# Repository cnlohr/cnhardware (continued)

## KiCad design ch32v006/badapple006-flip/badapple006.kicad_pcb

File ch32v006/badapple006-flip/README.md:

This has been moved to https://github.com/cnlohr/badderapple/tree/master/playback/ch32v006_hardware

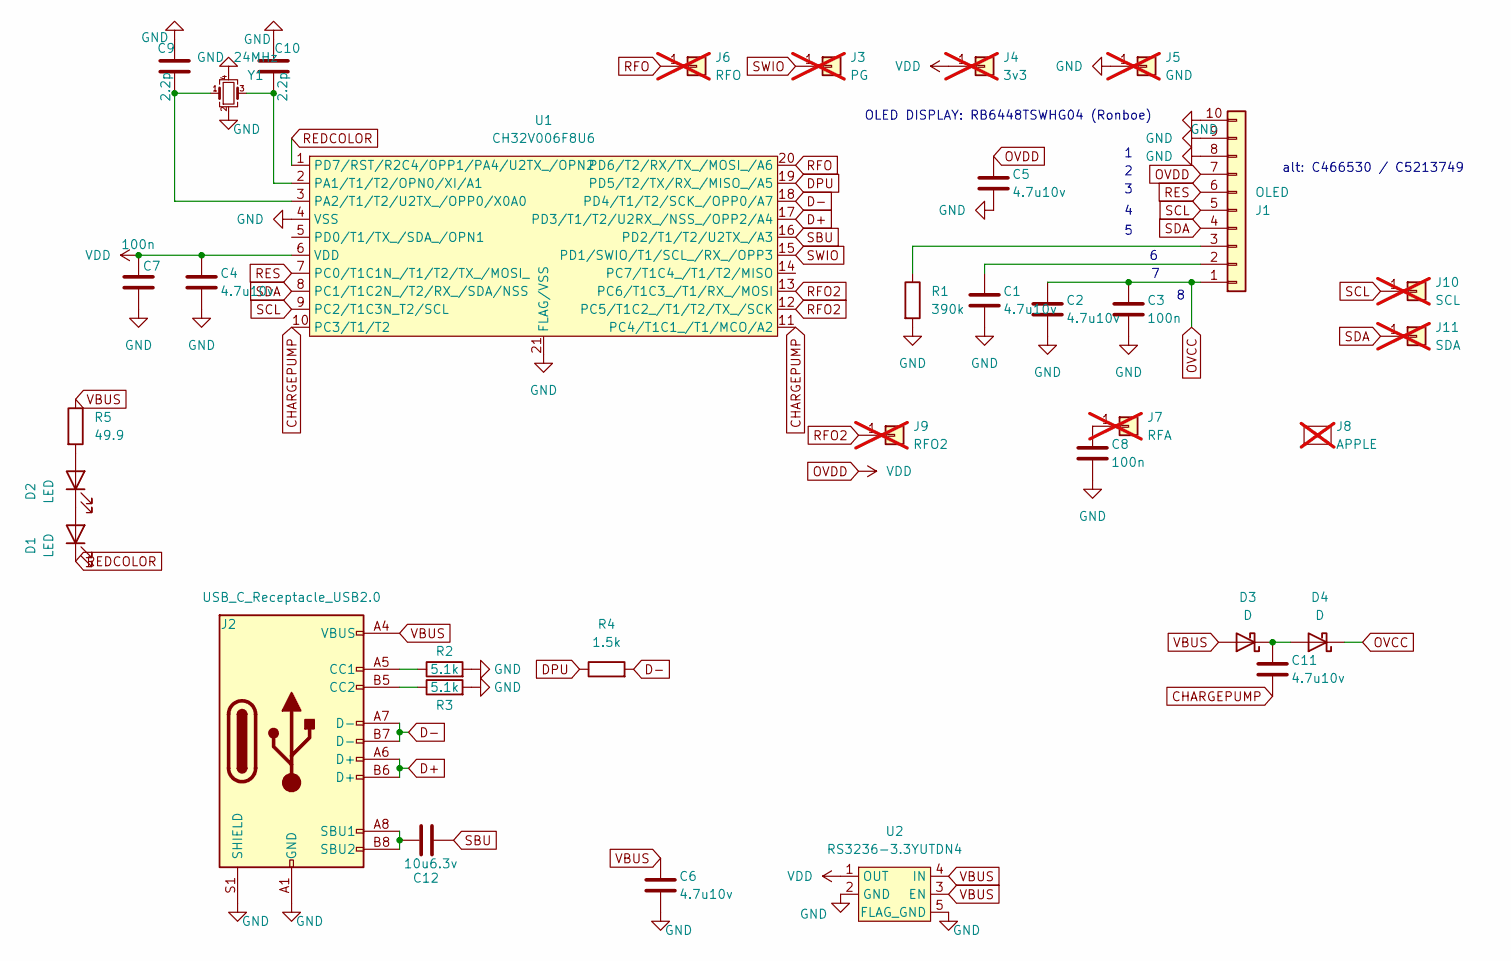
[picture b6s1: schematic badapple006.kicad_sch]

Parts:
C1, C2, C4, C5, C6, C11: 4.7u10v; C_0402_1005Metric; LCSC C23733
C3, C7, C8: 100n; C_0402_1005Metric; LCSC C1525
C9, C10: 2.2p; C_0402_1005Metric; LCSC C1559
C12: 10u6.3v; C_0402_1005Metric; LCSC C15525
D1, D2: LED; LED_0603_1608Metric; LCSC C2286
D3, D4: D; D_SOD-323; LCSC C191023
J1: OLED; AFC42-S08FMA-1H; LCSC C466530
J2: USB_C_Receptacle_USB2.0; USB_C_Receptacle_HRO_TYPE-C-31-M-12; LCSC C2765186
J3: PG; TestPoint_Pad_D1.0mm; not fitted
J4: 3v3; TestPoint_Pad_D1.0mm; not fitted
J5: GND; TestPoint_Pad_D1.0mm; not fitted
J6: RFO; TestPoint_Pad_D1.0mm; not fitted
J7: RFA; TestPoint_Pad_D1.0mm; not fitted
J8: APPLE; apple; not fitted
J9: RFO2; TestPoint_Pad_D1.0mm; not fitted
J10: SCL; TestPoint_Pad_D1.0mm; not fitted
J11: SDA; TestPoint_Pad_D1.0mm; not fitted
R1: 390k; R_0402_1005Metric; LCSC C25782
R2, R3: 5.1k; R_0402_1005Metric; LCSC C105872
R4: 1.5k; R_0402_1005Metric; LCSC C25867
R5: 49.9; R_0402_1005Metric; LCSC C25120
U1: CH32V006F8U6; QFN-20-1EP_3x3mm_P0.4mm_EP1.65x1.65mm; LCSC C42431288
U2: RS3236-3.3YUTDN4; xdfn-reg; LCSC C379350
Y1: 24MHz; Crystal_SMD_2016-4Pin_2.0x1.6mm; LCSC C2929397

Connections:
CHARGEPUMP: C11.2, U1.10 (PC3/T1/T2), U1.11 (PC4/T1C1_/T1/MCO/A2)
D+: J2.A6 (D+), J2.B6 (D+), U1.17 (PD3/T1/T2/U2RX_/NSS_/OPP2/A4)
D-: J2.A7 (D-), J2.B7 (D-), R4.2, U1.18 (PD4/T1/T2/SCK_/OPP0/A7)
DPU: R4.1, U1.19 (PD5/T2/TX/RX_/MISO_/A5)
GND: C1.2, C2.2, C3.2, C4.2, C5.2, C6.2, C7.2, C8.2, C9.1, C10.1, J1.8, J1.9, J1.10, J2.A1 (GND), J2.A12 (GND), J2.B1 (GND), J2.B12 (GND), J2.S1 (SHIELD), J5.1, R1.2, R2.2, R3.2, U1.4 (VSS), U1.21 (FLAG/VSS), U2.2 (GND), U2.5 (FLAG_GND), Y1.2, Y1.4
unnamed: D1.2 (A), D2.1 (K)
unnamed: D2.2 (A), R5.2
unnamed: C11.1, D3.1 (K), D4.2 (A)
unnamed: C1.1, J1.2
unnamed: J1.3, R1.1
unnamed: J2.A5 (CC1), R2.1
unnamed: J2.B5 (CC2), R3.1
unnamed: C12.2, J2.A8 (SBU1), J2.B8 (SBU2)
unnamed: C8.1, J7.1
unnamed: C10.2, U1.2 (PA1/T1/T2/OPN0/XI/A1), Y1.3
unnamed: C9.2, U1.3 (PA2/T1/T2/U2TX_/OPP0/X0A0), Y1.1
OVCC: C2.1, C3.1, D4.1 (K), J1.1
OVDD: C4.1, C5.1, C7.1, J1.7, J4.1, U1.6 (VDD), U2.1 (OUT)
REDCOLOR: D1.1 (K), U1.1 (PD7/RST/R2C4/OPP1/PA4/U2TX_/OPN2)
RES: J1.6, U1.7 (PC0/T1C1N_/T1/T2/TX_/MOSI_)
RFO: J6.1, U1.20 (PD6/T2/RX/TX_/MOSI_/A6)
RFO2: J9.1, U1.12 (PC5/T1C2_/T1/T2/TX_/SCK), U1.13 (PC6/T1C3_/T1/RX_/MOSI)
SBU: C12.1, U1.16 (PD2/T1/T2/U2TX_/A3)
SCL: J1.5, J10.1, U1.9 (PC2/T1C3N_T2/SCL)
SDA: J1.4, J11.1, U1.8 (PC1/T1C2N_/T2/RX_/SDA/NSS)
SWIO: J3.1, U1.15 (PD1/SWIO/T1/SCL_/RX_/OPP3)
VBUS: C6.1, D3.2 (A), J2.A4 (VBUS), J2.A9 (VBUS), J2.B4 (VBUS), J2.B9 (VBUS), R5.1, U2.3 (EN), U2.4 (IN)

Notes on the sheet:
alt: C466530 / C5213749
OLED DISPLAY: RB6448TSWHG04 (Ronboe)

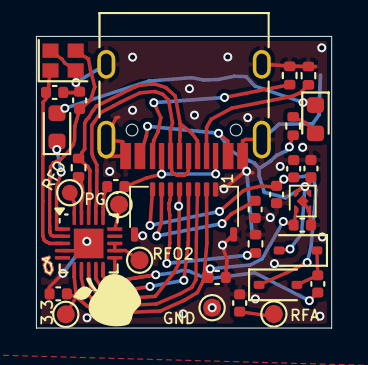
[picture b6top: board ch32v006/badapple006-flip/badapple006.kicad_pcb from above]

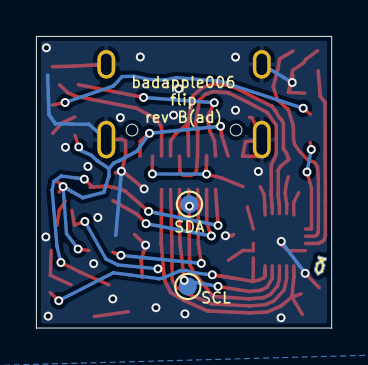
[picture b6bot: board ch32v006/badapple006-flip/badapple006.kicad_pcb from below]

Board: 2 copper layers, 16.4 x 16.2 mm, 35 parts (2 on the bottom side), 27 nets.

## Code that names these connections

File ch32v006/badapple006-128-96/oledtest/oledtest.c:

/* Small example showing how to use the SWIO programming pin to 
   do printf through the debug interface */

#include "ch32fun.h"
#include <stdio.h>

//#define SH1107
// Actually an SSD1327
#define SSD1327
#define SSD1306_FULLUSE
#define SSD1306_W (128) 
#define SSD1306_H (96*4)// For greyscale.
#define SSD1306_FULLUSE
#define SSD1306_OFFSET 0

#define SSD1306_RST_PIN PC3
#define SSD1306_CS_PIN PC1
#define SSD1306_DC_PIN PC2

#define SSD1306_MOSI_PIN PC6
#define SSD1306_SCK_PIN  PC5

#include "ssd1306_spi.h"
#include "ssd1306.h"

int main()
{
	SystemInit();
	funGpioInitAll();

	// On the 006, only GPIO_CFGLR_OUT_10Mhz_PP is available.

	funPinMode( PC4, GPIO_CFGLR_OUT_10Mhz_PP ); // BCTRL to 0.
	funDigitalWrite( PC4, 0 );

	// Power on
	funPinMode( PC0, GPIO_CFGLR_OUT_10Mhz_PP ); // Turn on OLED display.
	funDigitalWrite( PC0, 1 );

	ssd1306_rst();

	if( ssd1306_spi_init() || ssd1306_init() )
	{
		printf( "OLED FAILURE\n" );
	}

	static const uint8_t ssd1327_init_array[] =
	{

		0xAE, // Display off
		0xD5, 0x62, // Function Selection
		0xA8, 0x5F, // Set Multiplex Ratio
		0xA2, 0x20, // Set Display Offset
		0xA1, 0x60, // Set Display Start Line
		0xAB, 0x01, // Enable internal VDD regulator
		0xa0, 0x51, // Set Re-Map
		0xb1, 0x22, // Set phase length
		0x81, 0xdf, // Set Contrast Control
		0xbc, 0x10, // Set Pre-Charge voltage
		0xbe, 0x05, // Set VCOMH Deselect Level

		0xa4, // Normal display

		0xb6, 0x0a, // Set Second pre-charge Period
		0xaf, // Display On

//		0xa0, 0x51, // Set Re-Map

/*
		0xD5, 0x62, // Function Selection
		0xa0, 0x40, // Enable even-odd

		0xA2, 0x40, // Set Display Offset
		0xA1, 0x00, // Set Display Start Line
		0xAB, 0x01, // Enable internal VDD regulator

		0xb1, 0x22, // Set phase length
		0x81, 0xdf, // Set Contrast Control
		0xbc, 0x10, // Set Pre-Charge voltage
		0xbe, 0x05, // Set VCOMH Deselect Level

		// Bonus
		0xA8, 0x5F, // Set Multiplex Ratio
*/
	};
	int i;
	for( i = 0; i < sizeof( ssd1327_init_array ); i++ )
	{
		ssd1306_cmd( ssd1327_init_array[i] );
	}

	int x, y;
	int t = 0;

//	ssd1306_cmd( 0xA2 );
//	ssd1306_cmd( 0x60 );
//	ssd1306_cmd( 0xA1 );
//	ssd1306_cmd( 0x80 );


	while(1)
	{
		for( y = 0; y < 96; y++ )
		{
			for( x = 0; x < 128; x++ )
			{
				int gs = ((x*y+t)>>1)&0xf;
				if( x & 1 )
					ssd1306_buffer[(x>>1)+y*64] |= gs;
				else
					ssd1306_buffer[(x>>1)+y*64] = gs<<4;

				//ssd1306_buffer[(x>>1)+y*64] = y;//(y&1)?0xfa:0x00;
			}
		}
		t++;
		ssd1306_refresh();

/*	ssd1306_cmd( 0xA8 );
	ssd1306_cmd( 0x02 );
	ssd1306_cmd( 0xA8 );
	ssd1306_cmd( 0x3f );
	Delay_Us(100);
	ssd1306_cmd( 0xA8 );
	ssd1306_cmd( 0x02 );
*/
/*
	ssd1306_cmd( 0xA8 );
	ssd1306_cmd( 0x01 ); // Set Multiplex Ratio
	ssd1306_cmd( 0xA8 );
	ssd1306_cmd( 0x0f ); // Set Multiplex Ratio
	ssd1306_cmd( 0xA0 );
	ssd1306_cmd( 0x0f ); // Set start line
*/
	}
}

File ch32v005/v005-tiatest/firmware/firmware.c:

/* Small example showing how to use the SWIO programming pin to 
   do printf through the debug interface */

#include "ch32fun.h"
#include <stdio.h>

int main()
{
	SystemInit();

	RCC->APB2PCENR = RCC_APB2Periph_GPIOD | RCC_APB2Periph_GPIOC | RCC_APB2Periph_AFIO;

	// NSEL1 = 001 (PD0) = OPN1
	// MODE1 = 00 (PD4)
	// NSEL1 must be disconnected( how?)
	// PSEL  = 01 (PD7)

	funPinMode( PD4, GPIO_CFGLR_OUT_50Mhz_AF_PP ); // OPO
	funPinMode( PD7, GPIO_CFGLR_IN_FLOAT ); // OPP1
	funPinMode( PD0, GPIO_CFGLR_IN_FLOAT ); // OPN1

	// right now, 22k 1pF

	funPinMode( PD7,GPIO_CFGLR_OUT_50Mhz_AF_PP ); // OPP1 OVerride rail
	funDigitalWrite( PD7, 0 );

	// Mode 17.2.1.1 OPA Single-ended Input
	OPA->OPA_KEY = 0x45670123; // KEY1
	OPA->OPA_KEY = 0xCDEF89AB; // KEY2
	//OPA->CFGR1 = 0;
	OPA->CTLR1 = 
		OPA_CTLR1_OPA_HS1 |
		OPA_CTLR1_OPA_LOCK |
		OPA_CTLR1_NSEL1_CHN1 | // NSEL1 = PD0
		OPA_CTLR1_PSEL1_CHP1 | // PSEL1 = PD7
		0 | // MODE1 = 0 (PD4 Output)
		OPA_CTLR1_OPA_EN1 |
		OPA_CTLR1_FB_EN1 | // Extra feedback resistor (SOMETIMES IT GOOD SOMETIMES IT BAD)
		//OPA_CTLR1_VBEN | // Toying with + input - it lowers the voltage for more headroom but makes everything rattier.
		//OPA_CTLR1_VBSEL |
		0;

	//CMP1 has option to turn on +/- 24mV

	// To fiddle:
	// Disable/enable FB_EN1.

	// Comparators:
	// CMP2 = OPA out // CMP2_REF -> TIM1_BKIN
	// CMP2 cannot output directly.

	OPA->CTLR2 = 
		OPA_CTRL2_HYEN1 |
		0;
	
	while(1)
	{
		//printf( "%d\n",  );
	}
}
